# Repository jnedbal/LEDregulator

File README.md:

# LEDregulator
LED regulator electronics circuit for the [illuminated orbital shaker for microalgae cultures](https://app.labstep.com/sharelink/221d4460-8591-4ab5-ac0c-70b54c93532a).

The circuit serves two functions: It regulates the current to the LED illuminator and it controls fans cooling the LEDs.

There are two modes of operation supported by the circuit: The trickle current mode and the variable current mode.

The trickle current mode allows low current to flow throught the LEDs. This provides sufficient light to sustain the culture for long periods of time at a slow growth rate.

The variable current mode allows the user to choose from seven current settings using a rotary switch to vary the illumination light power delivered to the culture. In this mode, the cooling fans are switched on to keep the temperature of the culture close to the ambient temperature and avoid its overheating.

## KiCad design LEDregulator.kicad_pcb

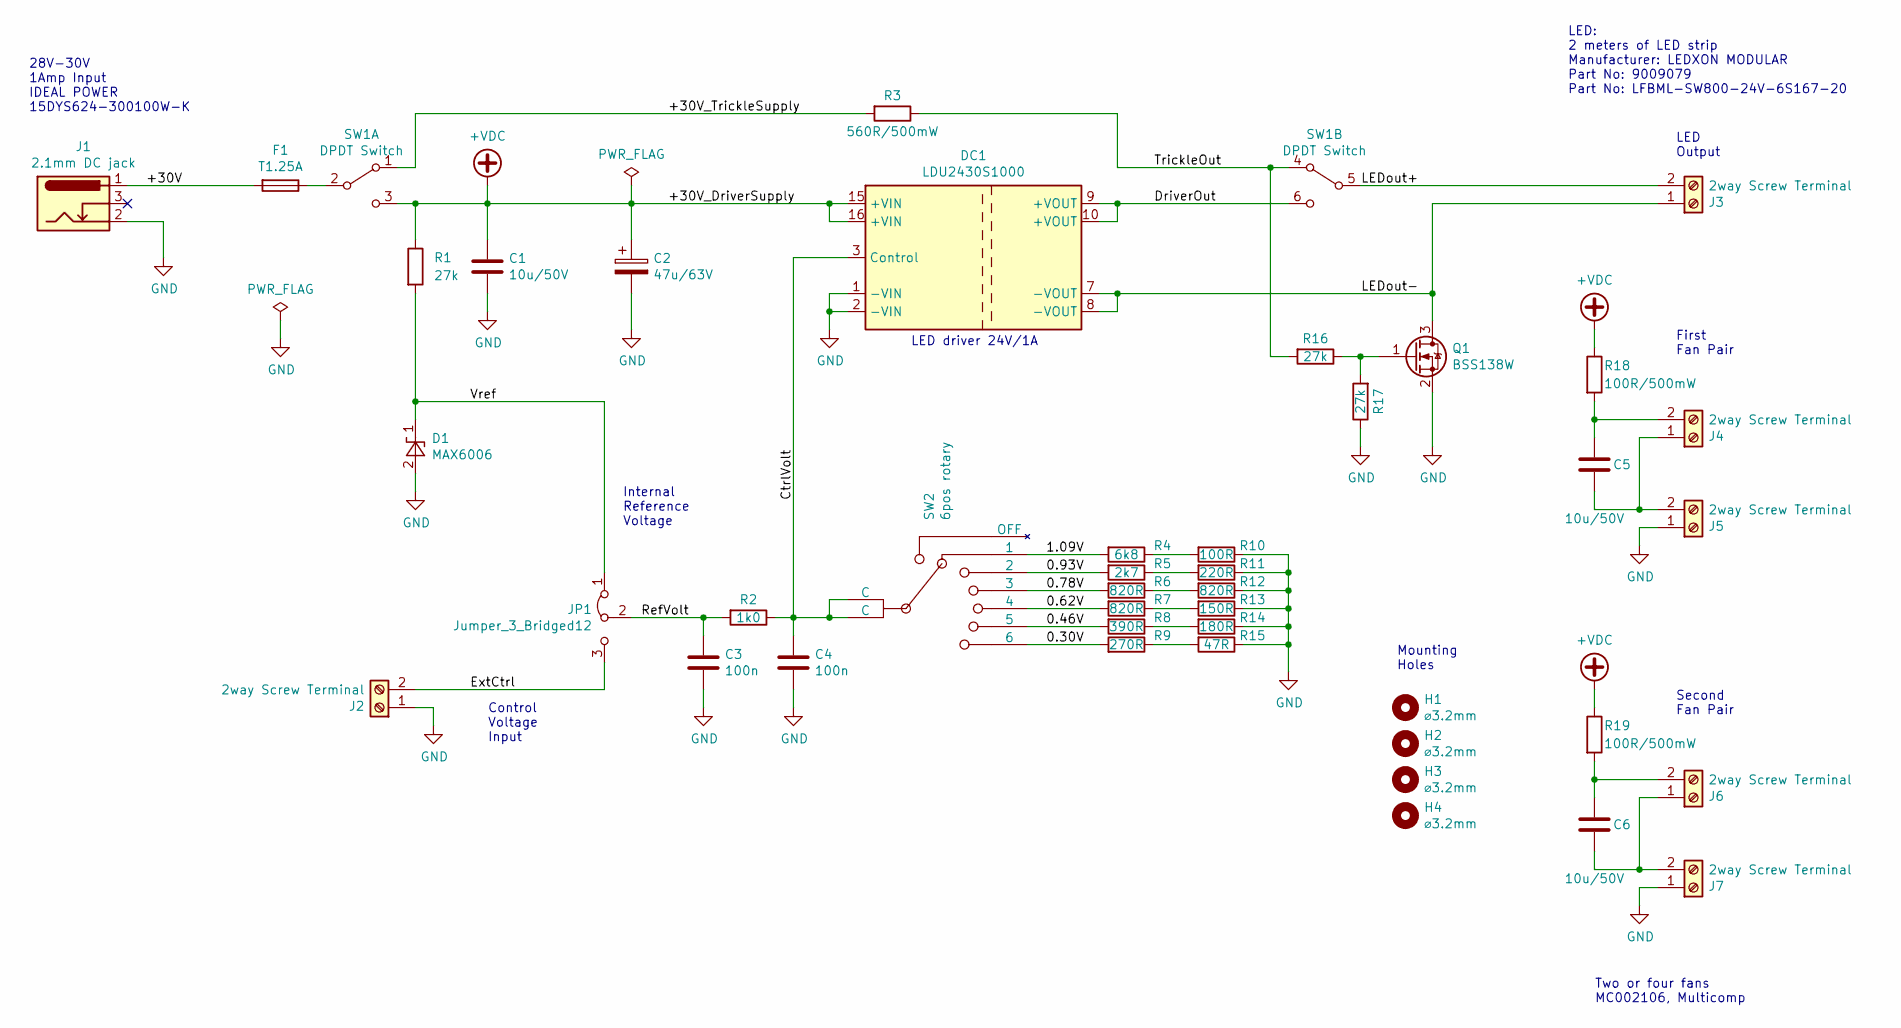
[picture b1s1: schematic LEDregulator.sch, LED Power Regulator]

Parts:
C1, C5, C6: 10u/50V; C_1206_3216Metric; Part Number GRT31CR61H106KE01L
C2: 47u/63V; CP_Elec_8x10.5; Part Number EEE1JA470UP
C3, C4: 100n; C_0603_1608Metric; Part Number MC0603B104K500CT
D1: MAX6006; SOT-23; Part Number MAX6006BEUR+T
DC1: LDU2430S1000; XPPOWER_LDU24; Part Number LDU2430S1000
F1: T1.25A; Fuseholder5x20_horiz_open_lateral_Type-II; Part Number 0751.0052
H1, H2, H3, H4: ⌀3.2mm; MountingHole_3.2mm_M3
J1: 2.1mm DC jack; 2.1mmBarrelJack; Part Number FC681478
J2, J3, J4, J5, J6, J7: 2way Screw Terminal; TerminalBlock_MetzConnect_Type086_RT03402HBLC_1x02_P3.81mm_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; Part Number MC000018
JP1: Jumper_3_Bridged12; Pin_Header_Straight_1x03_Pitch2.54mm; Part Number 2211S-03G
Q1: BSS138W; SOT-23; Part Number BSS138W-7-F
R1, R16, R17: 27k; R_0603_1608Metric; Part Number MCWR06X2702FTL
R2: 1k0; R_0603_1608Metric; Part Number MCWR06X1001FTL
R3: 560R/500mW; R_1206_3216Metric_Pad1.42x1.75mm_HandSolder; Part Number CRGH1206F560R
R4: 6k8; R_0603_1608Metric; Part Number MCWR06X6801FTL
R5: 2k7; R_0603_1608Metric; Part Number MCWR06X2701FTL
R6, R7, R12: 820R; R_0603_1608Metric; Part Number MCWR06X8200FTL
R8: 390R; R_0603_1608Metric; Part Number MCWR06X3900FTL
R9: 270R; R_0603_1608Metric; Part Number MCWR06X2700FTL
R10: 100R; R_0603_1608Metric; Part Number MCWR06X1000FTL
R11: 220R; R_0603_1608Metric; Part Number MCWR06X2200FTL
R13: 150R; R_0603_1608Metric; Part Number MCWR06X1500FTL
R14: 180R; R_0603_1608Metric; Part Number MCWR06X1800FTL
R15: 47R; R_0603_1608Metric; Part Number MCWF06P47R0FTL
R18, R19: 100R/500mW; R_1206_3216Metric_Pad1.42x1.75mm_HandSolder; Part Number CRGH1206F100R
SW1: DPDT Switch; switchDPDT; Part Number 1MD4T1B1M1QE
SW2: 6pos rotary; Nidec_Copal_SS-10-16; Part Number SS-10-16NP-LE

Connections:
+VDC: C1.1, C2.1, DC1.15 (+VIN), DC1.16 (+VIN), R1.1, R18.1, R19.1, SW1.3 (C)
/0.30V: R9.2, SW2.8 (6)
/0.46V: R8.2, SW2.6 (5)
/0.62V: R7.2, SW2.5 (4)
/0.78V: R6.2, SW2.4 (3)
/0.93V: R5.2, SW2.3 (2)
/1.09V: R4.2, SW2.1
/+30V: F1.2, J1.1
/+30V_TrickleSupply: R3.2, SW1.1 (A)
/CtrlVolt: C4.1, DC1.3 (Control), R2.1, SW2.2 (C), SW2.7 (C)
/DriverOut: DC1.9 (+VOUT), DC1.10 (+VOUT), SW1.6 (C)
/ExtCtrl: J2.2, JP1.3 (B)
/LEDout+: J3.2, SW1.5 (B)
/LEDout-: DC1.7 (-VOUT), DC1.8 (-VOUT), J3.1, Q1.3 (D)
/RefVolt: C3.1, JP1.2 (C), R2.2
/TrickleOut: R3.1, R16.2, SW1.4 (A)
/Vref: D1.1 (K), JP1.1 (A), R1.2
GND: C1.2, C2.2, C3.2, C4.2, D1.2 (A), DC1.1 (-VIN), DC1.2 (-VIN), J1.2, J2.1, J5.1, J7.1, Q1.2 (S), R10.1, R11.1, R12.1, R13.1, R14.1, R15.1, R17.1
unnamed: C5.1, J4.2, R18.2
unnamed: C5.2, J4.1, J5.2
unnamed: C6.1, J6.2, R19.2
unnamed: C6.2, J6.1, J7.2
unnamed: F1.1, SW1.2 (B)
unnamed: Q1.1 (G), R16.1, R17.2
unnamed: R4.1, R10.2
unnamed: R5.1, R11.2
unnamed: R6.1, R12.2
unnamed: R7.1, R13.2
unnamed: R8.1, R14.2
unnamed: R9.1, R15.2

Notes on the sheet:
Control Voltage Input
Internal Reference Voltage
LED Output
28V-30V 1Amp Input IDEAL POWER 15DYS624-300100W-K
Mounting Holes
LED driver 24V/1A
First Fan Pair
Second Fan Pair
Two or four fans MC002106, Multicomp
LED: 2 meters of LED strip Manufacturer: LEDXON MODULAR Part No: 9009079 Part No: LFBML-SW800-24V-6S167-20

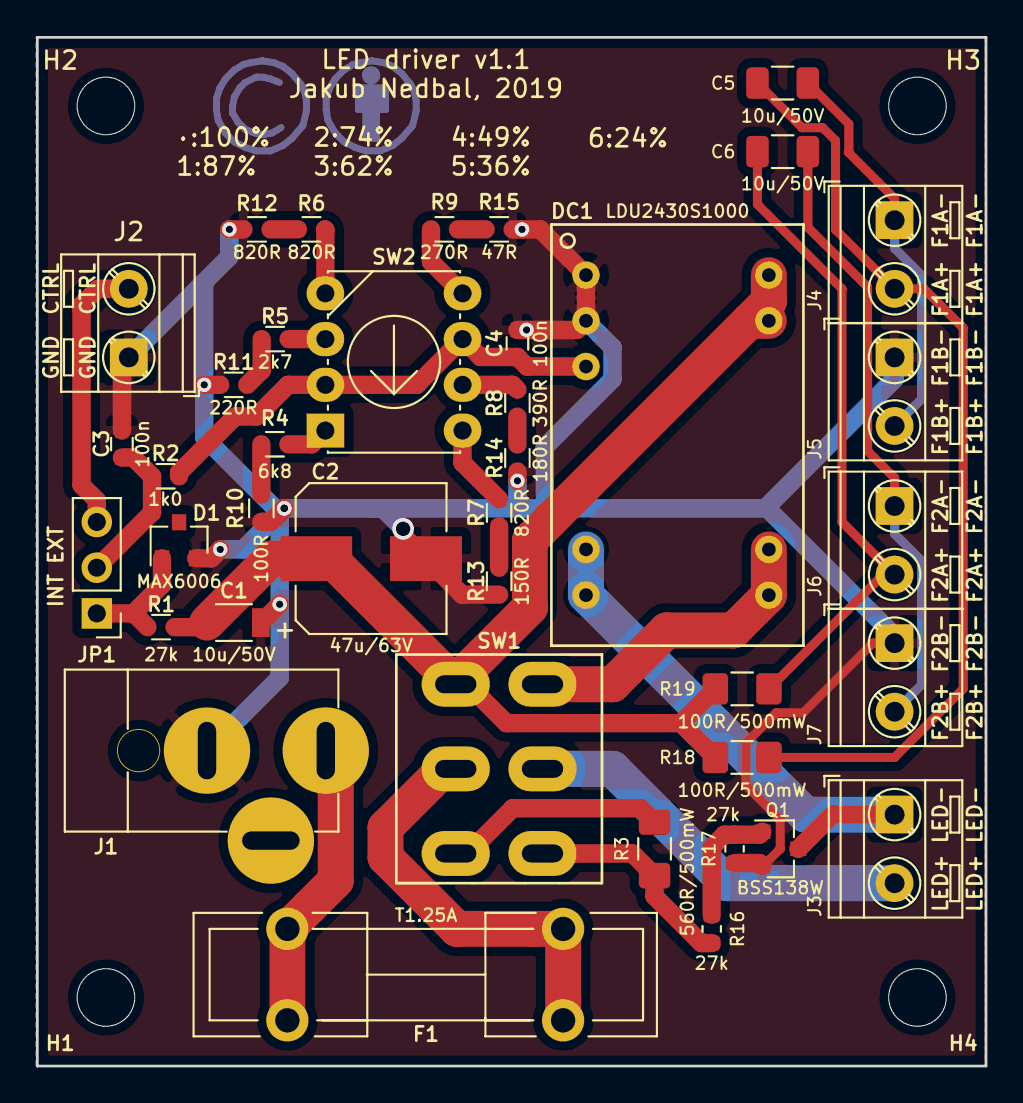
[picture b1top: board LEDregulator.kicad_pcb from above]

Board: 2 copper layers, 52.7 x 57.1 mm, 43 parts (0 on the bottom side), 30 nets.

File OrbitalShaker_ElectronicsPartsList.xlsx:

Item | Qty | Value | Description | Distributor | Manufacturer | Order Code | Part Number | Unit Price [£] | Total Price [£]
1 | 3 | 10u/50V | 10µF/50V 1206 ceramic capacitor (pack of 5) | Farnell | Murata | 2672214 | GRT31CR61H106KE01L | 0.525 | 2.625
2 | 1 | 47u/63V | 47µF/63V electrolytic capacitor | Farnell | Panasonic | 2326166 | EEE1JA470UP | 0.679 | 0.679
3 | 2 | 100n | 100nF/50V X7R 0603 ceramic capacitor (pack of 10) | Farnell | Multicomp | 1759122 | MC0603B104K500CT | 0.0341 | 0.341
4 | 1 | MAX6006 | 1.25V shunt reference | Farnell | Maxim Integrated | 2511278 | MAX6006BEUR+T | 1.29 | 1.29
5 | 1 | LDU2430S1000 | 24V/1A adjustable LED driver | Farnell | XP Power | 1738296 | LDU2430S1000 | 8.23 | 8.23
6 | 1 | Fuse Holder | 5x20mm fuse holder (pack of 10) | Farnell | Schurter | 2309093 | 751.0052 | 0.103 | 1.03
7 | 1 | T1.25A | 1.25A slow-burning fuse (pack of 10) | Farnell | Eaton Bussmann | 1123242 | S506-1.25-R | 0.836 | 8.36
8 | 1 | 2.1mm DC Jack | 2.1mm 2A/16V DC power jack | Farnell | Cliff Electronics | 2450496 | FC681478 | 1.84 | 1.84
9 | 6 | 2way Screw Terminal | 2way 3.81mm screw terminal | Farnell | Multicomp | 2007985 | MC000018 | 0.481 | 2.886
10 | 1 | 3way Shunt Header | 3way 2.54mm header (pack of 50) | Farnell | Multicomp | 1593412 | 2211S-03G | 0.0156 | 0.78
11 | 1 | Shunt Jumper | 2.54 mm shunt jumper (pack of 50) | Farnell | Multicomp | 2834673 | MC-2228CG | 0.0262 | 1.31
12 | 1 | BSS138W | 50V 200mA N-channel MOSFET (pack of 5) | Farnell | Diodes | 1713833 | BSS138W-7-F | 0.265 | 1.325
13 | 3 | 27k | 27kΩ 0603 1% SMD resistor (pack of 10) | Farnell | Multicomp | 2447315 | MCWR06X2702FTL | 0.0038 | 0.038
14 | 1 | 1k0 | 1kΩ 0603 1% SMD resistor (pack of 10) | Farnell | Multicomp | 2447272 | MCWR06X1001FTL | 0.0038 | 0.038
15 | 1 | 560R/500mW | 560Ω 1206 1% 500mW SMD resistor (pack of 10) | Farnell | TE Connectivity | 2332136 | CRGH1206F560R | 0.0447 | 0.447
16 | 1 | 6k8 | 6.8kΩ 0603 1% SMD resistor (pack of 10) | Farnell | Multicomp | 2447427 | MCWR06X6801FTL | 0.0034 | 0.034
17 | 1 | 2k7 | 2.7kΩ 0603 1% SMD resistor (pack of 10) | Farnell | Multicomp | 2447324 | MCWR06X2701FTL | 0.0034 | 0.034
18 | 3 | 820R | 820Ω 0603 1% SMD resistor (pack of 10) | Farnell | Multicomp | 2447437 | MCWR06X8200FTL | 0.0035 | 0.035
19 | 1 | 390R | 390Ω 0603 1% SMD resistor (pack of 10) | Farnell | Multicomp | 2447353 | MCWR06X3900FTL | 0.0037 | 0.037
20 | 1 | 270R | 270Ω 0603 1% SMD resistor (pack of 10) | Farnell | Multicomp | 2447314 | MCWR06X2700FTL | 0.0038 | 0.038
21 | 1 | 100R | 100Ω 0603 1% SMD resistor (pack of 10) | Farnell | Multicomp | 2447227 | MCWR06X1000FTL | 0.0034 | 0.034
22 | 1 | 220R | 220Ω 0603 1% SMD resistor (pack of 10) | Farnell | Multicomp | 2447298 | MCWR06X2200FTL | 0.0034 | 0.034
23 | 1 | 150R | 150Ω 0603 1% SMD resistor (pack of 10) | Farnell | Multicomp | 2447255 | MCWR06X1500FTL | 0.0035 | 0.035
24 | 1 | 180R | 180Ω 0603 1% SMD resistor (pack of 10) | Farnell | Multicomp | 2447267 | MCWR06X1800FTL | 0.0034 | 0.034
25 | 1 | 47R | 47Ω 0603 1% SMD resistor (pack of 10) | Farnell | Multicomp | 2694082 | MCWF06P47R0FTL | 0.0083 | 0.083
26 | 2 | 100R/500mW | 100Ω 1206 1% 500mW SMD resistor (pack of 10) | Farnell | TE Connectivity | 2332126 | CRGH1206F100R | 0.0423 | 0.423
27 | 1 | DPDT Switch | DPDT On-Off-On toggle switch | Farnell | Multicomp | 9473556 | 1MD4T1B1M1QE | 2.6 | 2.6
28 | 1 | 6pos Rotary Switch | 6-position rotary switch | Farnell | Nidec Copal | 2854809 | SS-10-16NP-LE | 2.48 | 2.48
29 | 1 | DIP-8 Socket | DIP-8 socket for rotary switch | Farnell | Multicomp | 2668408 | SPC15494 | 0.133 | 1.33
30 | 4 | 40mm Fan | 12 VDC Fan, 60mA, 40mm | Farnell | Multicomp | 2816685 | MC002106 | 1.98 | 7.92
31 | 2 | 1m LED Strip | LED strip, 1m, cool white, 24VDC, 14.4W | Farnell | Ledxon Modular | 2214009 | 9009079 | 25.84 | 51.68
32 | 1 | 30V/1A AC Adaptor | 30V/1A 2.1mm DC power supply | Farnell | Ideal Power | 2771453 | 15DYS624-300100W-K | 23.37 | 23.37
33 | 4 | 50mm M4 Standoff | 50mm M4 standoff male-female | Farnell | Ettinger | 1466738 | 05.14.501 | 0.73 | 2.92
Total |  |  |  |  |  |  |  |  | 124.34

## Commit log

2019-05-24 First commit. Schematics is ready
2019-05-24 Added first board components
2019-05-27 Laid out PCB components
2019-06-02 Laid out the PCB
2019-06-07 Board ready
2019-06-16 Initial commit. Sent for manufacture.
2019-06-17 Fixed the production files by removing margin and adding Edge.
2019-07-16 Updated several part details with alternative suppliers
2019-07-24 Fixed barrel jack 2.1mm to have wider holes
2019-08-08 Final commit after using on a new computer before a v1.1 branch is created
2019-08-08 Started a new branch (v1.1) that has got fan control, low-side switch on the LED for trickle current and power resistors. Also the 5.08mm terminal connectors have been changed to more compact 3.81mm.
2019-08-08 Added labels for the types of fans and LED strips used. Changed the 3D package of the DC input connector.
2019-08-09 Finished boards for production of version 1.1. This version has got a floating LED output and adds support for fans.
2019-09-09 3D models ready
2019-09-13 Added license file.
2019-11-13 Added parts list Excell file and tidies up the schematics a bit
2020-01-08 Update README.md
    Changed title of the project from "algal" to "microalgae"
2020-01-13 Changed and updated the parts list
2020-01-13 Removed old Parts list
2020-01-13 Cleaned up the Parts List
2020-02-17 Minor fixes to the Parts list

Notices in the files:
LEDregulator.kicad_pcb:
CC-BY-SA
